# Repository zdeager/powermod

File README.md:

# PowerMOD

A generic power scheduler, UPS, and battery supply for I2C-capable hosts — Linux SBCs, microcontrollers, anything with a 3.3V I2C bus and a power input to control. Real-time clock, scheduled power-cycling, battery backup with load switchover, opt-in watchdog, and an event log, at a component cost of ≈$2.90.

**Status: design complete on paper. No hardware exists yet.** Every part is selected, priced, and datasheet-verified; every net is mapped pin-for-pin; the register map is ready for firmware review. Next step: transcribe the netlist into an EDA tool and lay out the board.

## Documents

| File | What it is |
|---|---|
| [powermod-spec.md](powermod-spec.md) | **The source of truth.** Full decision record with reasoning history — including reversed decisions, retained and marked. Carries the net map, the semantic-review findings, and a 45-claim verification register (every part capability cited to its datasheet; 18 claims were false and each correction is documented) |
| [powermod-user-guide-draft.md](powermod-user-guide-draft.md) | Draft user manual — integration guide, LED states, scheduling patterns, FAQ, and honest limits (drift table, output-current table, weak-supply behavior) |
| [powermod-register-map.md](powermod-register-map.md) | I2C protocol v1 — 32 registers, wire-level reference for host integration and firmware |
| [powermod-schematic.md](powermod-schematic.md) | Pin-exact netlist — every component pin to every net, MCU pin assignment, capture-time checklist. The EDA schematic transcribes this |
| [powermod-bom.md](powermod-bom.md) | Bill of materials — LCSC part numbers, verified prices, do-not-substitute notes, sourcing flags |
| [powermod_full_state_machine.svg](powermod_full_state_machine.svg) | Power state machine — all states, transitions, and gating rules |
| [hardware/](hardware/) | KiCad transcription — `netlist.py` (machine source of truth + validator) generates `powermod.net`, `powermod.kicad_sch` (ERC-clean, round-trip-verified), and via `layout.py` a placed, DRC-clean `powermod.kicad_pcb` (routing pending) |

## Open items (all require hardware)

Converter efficiency, standby current, the `CE` battery-detect decay test, factory-reset gesture feel, Q1/Q2 handover scope check.

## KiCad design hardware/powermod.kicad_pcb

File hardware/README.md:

# PowerMOD hardware

Machine-generated PCB design for a Raspberry Pi Zero 2 W power scheduler /
UPS / battery board. The electrical design is defined in code (`netlist.py`);
the board was laid out and routed with the scripted KiCad + Freerouting
toolchain below, then hand-finished.

## The board — `powermod.kicad_pcb` (final)

65 × 40 mm, 4-layer (F.Cu signal / In1 solid GND / In2 signal / B.Cu signal).
Bolts under a Pi Zero 2 W (holes on the Pi's 58×23 grid, flush to the N+W
edges); the Pi covers y0–30, and all user-facing parts (USB-C out, battery,
button, LEDs, jumpers, test pads) sit on the exposed strip below it.
Single-sided assembly.

One KiCad project, one stem: `powermod.kicad_pro` (netclasses + DRC config),
`powermod.kicad_sch` (generated schematic), `powermod.kicad_pcb` (board),
`powermod.kicad_dru` (width-enforcement rules — net classes alone are NOT
checked by DRC).

**Status: fab-ready.** Fully routed, 0 unconnected, 0 clearance; the only DRC
items are 4 `track_width` flags on the L2/L1N necks at U3's 0.65 mm pins,
which physically cannot be 1.0 mm wide. Pre-fab audit (pad-for-pad netlist
diff, datasheet pin checks, operating-point math, the D5 supercap fix):
see **`PREFAB_AUDIT.md`** — read it before ordering (BOM traps, firmware
contract, bring-up plan).

> **Do NOT regenerate this board from `netlist.py`.** Placement and the
> USB-C fine-pitch escapes are hand-done. Make changes surgically on
> `powermod.kicad_pcb` and update `netlist.py` in parallel, then prove they
> agree with a pad-diff (the audit doc describes it).

## Electrical source of truth

- **`netlist.py`** — every component, pin, and net (73 components, 45 nets).
  Run it to (re)generate `powermod.kicad_sch`, `powermod.net`,
  `powermod.kicad_sym`, `sym-lib-table`, `fp-lib-table`. Has a self-test
  (golden vectors, pin counts).
- **`powermod.pretty/`** — local footprint lib: the merged-pad USB-C
  receptacle (reversible twin pads share one pad, so VBUS/GND escape cleanly
  and DRC sees no coincident-pad conflicts). Required to open the board.

## Reusable tools

All the layout/routing/placement scripts live in **`tools/`** (run them from
this directory, e.g. `python3 tools/finish_board.py powermod.kicad_pcb`, so
board paths and `_sizes.json` resolve; they add the parent dir to `sys.path`
to import `netlist.py`). `netlist.py` itself stays here — it's the design
source and writes the deliverables alongside itself. SPICE decks are in
`tools/spice/`.

Routing pipeline (for derivative boards — not this one):
- **`fr_pipeline.py`** — strip copper + export Specctra DSN / import routed
  SES. Freerouting must never see a pre-routed board.
- `tools/freerouting.jar` (gitignored, ~55 MB) — the autorouter. Java 21+, run
  with `-Djava.awt.headless=true` or it hangs on macOS.
- **`finish_board.py`** — post-route finisher: SES import → GND stitching →
  floating-pour-island tie vias → zone refill. Then DRC with
  `--refill-zones` (without it you get hundreds of phantom violations).
- **`stitch_gnd.py`** — the 2.5 mm GND stitching-via grid to the In1 plane.
- **`close_nets.py`** — route leftover nets with the In2-capable grid A*,
  each route validated by refill+DRC and reverted if it doesn't improve.
- **`router.py`** — grid A* + obstacle model (F/In2/B) used by the above.
- **`netclasses.py`** — inject net-class width targets into a `.kicad_pro`.

Placement:
- **`layout_v2.py`** — the board generator (`gen_pcb`: footprints, GND
  planes, keepouts). `layout_mount.py` configures it for this board's
  outline/holes/pinned I/O.
- **`place_constrained.py`** — constraint-aware force-directed placer
  (net springs, padded repulsion, wide-net/IC halos, rigid converter block).
- **`place_search_mount.py`** / **`relax_mount.py`** — placement search
  scored by Freerouting / overlap relaxer. **`mount_best.py`** — placer
  output snapshot (stale vs the hand-edited board; the board is
  authoritative).
- **`place_check.py`** — courtyard-overlap + off-board report.
- **`make_stencil.py`** — generates a bare user-facing-parts canvas for
  human I/O placement (its output board was removed once the layout froze).
- `_sizes.json` — cached footprint courtyard sizes (kept in this dir; the
  placer reads it cwd-relative).

SPICE (`tools/spice/`):
- **`power_path_scenarios.py`** — behavioural ngspice model of the Q1/Q2/Q3
  power path; runs the startup/switchover/unplug scenario matrix (see the
  SPICE section of `PREFAB_AUDIT.md`). Needs `ngspice` on PATH.

## Hard-won rules (cost real time — don't relearn them)

- A green DRC only checks rules that exist: keep `powermod.kicad_dru` next
  to the board, and after any rename/move confirm the 4 known `track_width`
  flags still fire (if they vanish, the rules got orphaned, not fixed).
- Netclasses live in the `.kicad_pro`. A board file copied away from its
  project routes everything at 0.2 mm and "routes fully" — a fake win.
- Zone fills are stored in the file: refill before DRC or judging renders.
- Scripted tracks don't bind to large connector pads (USB-C, bar pads) —
  those few escapes are interactive-routing territory; small pads bind fine.

## History

v1 (58×40, 2-layer) had 3A rails at 0.2 mm (the `.kicad_dru` lesson); v2
(65×30) was superseded by this board; the QFN-package MCU was swapped for the
SOIC-20 ATtiny1616 to break the routing wall; `powermod_mount.*` was renamed
to `powermod.*` once it became the only board (2026-07-17); then the MCU
migrated **ATtiny1616 → PY32F003F18P6** (TSSOP-20, ARM Cortex-M0+) on the
`instock-parts` branch (2026-07-18) for JLC assembly availability, with a full
reroute — the current board is 65×40, 4-layer, PY32. Lessons live in
the tools and `PREFAB_AUDIT.md`, not in stale board files.

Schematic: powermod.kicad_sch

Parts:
C1, C2, C7: 10u; C_0805_2012Metric
C3, C4, C5: 22u; C_0805_2012Metric
C6: 4.7u; C_0603_1608Metric
C8, C9: 1u; C_0603_1608Metric
C10, C11, C12, C13, C14, C15, C16: 100n; C_0402_1005Metric
D1, D2: TJ-S3227; LED_TJ-S3227_RG_3.2x2.7mm
D3, D4, D5: 1N4148WS; D_SOD-323
J1: USB_C_IN; USB_C_Receptacle_TYPE-C_16P_PowerMerged
J2: USB_C_OUT; USB_C_Receptacle_TYPE-C_16P_PowerMerged
J3: JST_PH_2; JST_PH_S2B-PH-K_1x02_P2.00mm_Horizontal
J4: STEMMA_QT; JST_SH_SM04B-SRSS-TB_1x04-1MP_P1.00mm_Horizontal
J5: SWD_HDR; PinHeader_1x04_P2.54mm_Vertical
JP1: CHG_JUMPER; SolderJumper-2_P1.3mm_Open_RoundedPad1.0x1.5mm
JP2: VSEL_JUMPER; SolderJumper-2_P1.3mm_Open_RoundedPad1.0x1.5mm
L1: 1.5uH; L_Sumida_CDMC6D28_7.25x6.5mm
Q1, Q2: AON7407; DFN-8-1EP_3x3mm_P0.65mm_EP1.6x2.56mm
Q3: BSS138; SOT-23
R1: 1.2k; R_0402_1005Metric
R2, R3: 5.1k; R_0402_1005Metric
R4, R5: 56k; R_0402_1005Metric
R6, R8, R25: 1M; R_0402_1005Metric
R7, R9: 330k; R_0402_1005Metric
R10, R12, R13, R14, R28: 100k; R_0402_1005Metric
R11: 47k; R_0402_1005Metric
R15, R16, R17, R18, R19: 10k; R_0402_1005Metric
R20, R21, R22, R23: 560; R_0402_1005Metric
R24: 180k; R_0402_1005Metric
R26: 620k; R_0402_1005Metric
R27: 1k; R_0402_1005Metric
SW1: BUTTON; SW_SPST_PTS647_Sx50
TP1: VBACKUP_PAD; TestPoint_Pad_2.0x2.0mm
TP2: BAT_PAD; TestPoint_Pad_2.0x2.0mm
TP3: VOUT_PAD; TestPoint_Pad_2.0x2.0mm
TP4: GND_PAD; TestPoint_Pad_2.0x2.0mm
TP5: VBACKUP_GND_PAD; TestPoint_Pad_2.0x2.0mm
TP6: VOUT_GND_PAD; TestPoint_Pad_2.0x2.0mm
U1: BM8563ESA; SOIC-8_3.9x4.9mm_P1.27mm
U2: PY32F003F18P6; TSSOP-20_4.4x6.5mm_P0.65mm
U3: TPS63020DSJR; VSON-14-1EP_3x4.45mm_P0.65mm_EP1.6x4.2mm
U4: TP4056; SOIC-8-1EP_3.9x4.9mm_P1.27mm_EP2.29x3mm
U5: XC6206P332MR; SOT-23
Y1: Q13FC13500004; Crystal_SMD_3215-2Pin_3.2x1.5mm

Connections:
3V3: C9.1, C14.1, D3.2 (A), R15.1, R16.1, R17.1, R18.1, R19.1, R27.1, U2.9 (VDD), U5.2 (VOUT)
BUTTON: SW1.1 (A), U2.20 (PA1/BUTTON)
CC1_IN: J1.A5 (CC1), R2.1
CC1_OUT: J2.A5 (CC1), R5.1
CC2_IN: J1.B5 (CC2), R3.1
CC2_OUT: J2.B5 (CC2), R4.1
CHG_CE: R28.2, U2.5 (PA6/CHG_CE), U4.8 (CE)
CHG_CHRG: R15.2, U2.12 (PB5/CHG_CHRG), U4.7 (CHRG)
CHG_JP: D5.2 (A), R27.2
CHG_JPD: D5.1 (K), JP1.1 (A)
CHG_STDBY: R16.2, U2.6 (PA7/CHG_STDBY), U4.6 (STDBY)
CONV_EN: R14.1, U2.2 (PA3/CONV_EN), U3.12 (EN)
D1_GRN: D1.2 (A_GRN), R21.2
D1_RED: D1.3 (A_RED), R20.2
D2_GRN: D2.2 (A_GRN), R23.2
D2_RED: D2.3 (A_RED), R22.2
FB: R24.1, R25.1, U3.3 (FB)
FB_MID: JP2.1 (A), R25.2, R26.1
GND: C1.2, C2.2, C3.2, C4.2, C5.2, C6.2, C7.2, C8.2, C9.2, C10.2, C11.2, C13.2, C14.2, C15.2, C16.2, D1.1 (K_GRN), D1.4 (K_RED), D2.1 (K_GRN), D2.4 (K_RED), J1.A1 (GND), J1.A12 (GND), J1.SH (SHIELD), J2.A1 (GND), J2.A12 (GND), J2.SH (SHIELD), J3.2 (BAT-), J4.1 (GND), J5.1 (GND), Q3.2 (S), R1.2, R2.2, R3.2, R7.2, R9.2, R12.2, R13.2, R14.2, R24.2, SW1.2 (B), TP4.1, TP5.1, TP6.1, U1.4 (VSS), U2.7 (VSS), U3.2 (GND), U3.13 (PS/SYNC), U3.15 (PGND), U4.1 (TEMP), U4.3 (GND), U4.9 (PAD), U5.1 (VSS)
L1N: L1.1, U3.8 (L1), U3.9 (L1)
L2: L1.2, U3.6 (L2), U3.7 (L2)
LED_BAT_A: J5.3 (SWDIO), R22.1, U2.10 (PA13/SWDIO/LED_BAT_A)
LED_BAT_B: J5.2 (SWCLK), R23.1, U2.11 (PA14/SWCLK/LED_BAT_B)
LED_PWR_A: R20.1, U2.19 (PA0/LED_PWR_A)
LED_PWR_B: R21.1, U2.15 (PF4/BOOT0/LED_PWR_B)
NRST: J5.4 (NRST), U2.18 (PF2/NRST)
OSCI: U1.1 (OSCI), Y1.1 (X1)
OSCO: U1.2 (OSCO), Y1.2 (X2)
PROG: R1.1, U4.2 (PROG)
Q1_GATE: C12.2, Q1.4 (G), R10.2, R11.1
Q1_GATE_DRV: Q3.1 (G), R13.1, U2.1 (PA2/Q1_GATE_DRV)
Q3_DRAIN: Q3.3 (D), R11.2
RTC_INT: R19.2, U1.3 (INT), U2.8 (PA12/RTC_INT)
RTC_SCL: R18.2, U1.6 (SCL), U2.17 (PF1/RTC_SCL)
RTC_SDA: R17.2, U1.5 (SDA), U2.16 (PF0/RTC_SDA)
RTC_VDD: C13.1, D3.1 (K), D4.1 (K), U1.8 (VDD)
SCL: J4.4 (SCL), U2.13 (PB6/I2C_SCL)
SDA: J4.3 (SDA), U2.14 (PB7/I2C_SDA)
VBACKUP: D4.2 (A), JP1.2 (B), TP1.1
VBAT: C6.1, J3.1 (BAT+), Q2.5 (D), Q2.6 (D), Q2.7 (D), Q2.8 (D), Q2.9 (D), R6.1, TP2.1, U4.5 (BAT)
VBAT_DIV: C10.1, R6.2, R7.1, U2.3 (PA4/VBAT_SENSE)
VBUS: C7.1, C15.1, J1.A4 (VBUS), J1.A9 (VBUS), Q1.5 (D), Q1.6 (D), Q1.7 (D), Q1.8 (D), Q1.9 (D), Q2.4 (G), R8.1, R12.1, R28.1, U4.4 (VCC)
VBUS_DIV: C11.1, R8.2, R9.1, U2.4 (PA5/VBUS_SENSE)
VOUT: C3.1, C4.1, C5.1, J2.A4 (VBUS), J2.A9 (VBUS), JP2.2 (B), R4.2, R5.2, R26.2, TP3.1, U3.4 (VOUT), U3.5 (VOUT)
VSYS: C1.1, C2.1, C8.1, C12.1, C16.1, Q1.1 (S), Q1.2 (S), Q1.3 (S), Q2.1 (S), Q2.2 (S), Q2.3 (S), R10.1, U3.1 (VINA), U3.10 (VIN), U3.11 (VIN), U5.3 (VIN)

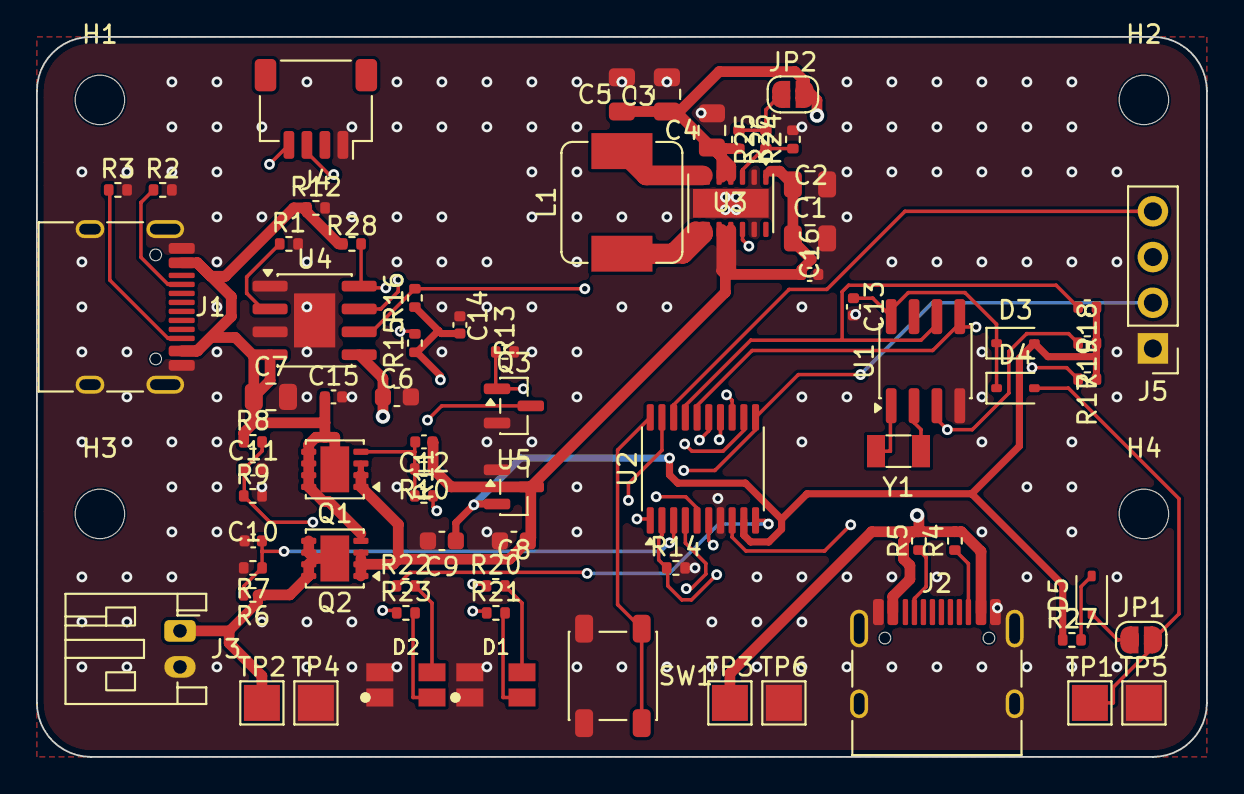
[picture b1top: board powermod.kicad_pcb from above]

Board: 4 copper layers, 65.0 x 40.0 mm, 77 parts (0 on the bottom side), 45 nets.

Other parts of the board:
H1, H2, H3, H4: M2.5; MountingHole_2.7mm_M2.5

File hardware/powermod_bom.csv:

"Comment","Designator","Footprint","LCSC Part #"
"10u","C1,C2,C7","C_0805_2012Metric","C15850"
"100n","C10,C11,C12,C13,C14,C15,C16","C_0402_1005Metric","C1525"
"22u","C3,C4,C5","C_0805_2012Metric","C45783"
"4.7u","C6","C_0603_1608Metric","C19666"
"1u","C8,C9","C_0603_1608Metric","C5673"
"TJ-S3227","D1,D2","LED_TJ-S3227_RG_3.2x2.7mm","C601677"
"1N4148WS","D3,D4,D5","D_SOD-323","C51898295"
"USB_C_IN","J1","USB_C_Receptacle_TYPE-C_16P_PowerMerged","C165948"
"USB_C_OUT","J2","USB_C_Receptacle_TYPE-C_16P_PowerMerged","C165948"
"JST_PH_2","J3","JST_PH_S2B-PH-K_1x02_P2.00mm_Horizontal",""
"STEMMA_QT","J4","JST_SH_SM04B-SRSS-TB_1x04-1MP_P1.00mm_Horizontal","C51940130"
"SWD_HDR","J5","PinHeader_1x04_P2.54mm_Vertical",""
"1.5uH","L1","L_Sumida_CDMC6D28_7.25x6.5mm","C5189751"
"AON7407","Q1,Q2","DFN-8-1EP_3x3mm_P0.65mm_EP1.6x2.56mm","C176756"
"BSS138","Q3","SOT-23","C52895"
"1.2k","R1","R_0402_1005Metric","C25862"
"100k","R10,R12,R13,R14,R28","R_0402_1005Metric","C25741"
"47k","R11","R_0402_1005Metric","C25792"
"10k","R15,R16,R17,R18,R19","R_0402_1005Metric","C25744"
"5.1k","R2,R3","R_0402_1005Metric","C25905"
"560","R20,R21,R22,R23","R_0402_1005Metric","C25126"
"180k","R24","R_0402_1005Metric","C25760"
"620k","R26","R_0402_1005Metric","C270590"
"1k","R27","R_0402_1005Metric","C11702"
"56k","R4,R5","R_0402_1005Metric","C25796"
"1M","R6,R8,R25","R_0402_1005Metric","C26083"
"330k","R7,R9","R_0402_1005Metric","C25778"
"BUTTON","SW1","SW_SPST_PTS647_Sx50","C2799414"
"BM8563ESA","U1","SOIC-8_3.9x4.9mm_P1.27mm","C269877"
"PY32F003F18P6","U2","TSSOP-20_4.4x6.5mm_P0.65mm","C5379864"
"TPS63020DSJR","U3","VSON-14-1EP_3x4.45mm_P0.65mm_EP1.6x4.2mm","C15483"
"TP4056","U4","SOIC-8-1EP_3.9x4.9mm_P1.27mm_EP2.29x3mm","C382139"
"XC6206P332MR","U5","SOT-23","C5446"
"Q13FC13500004","Y1","Crystal_SMD_3215-2Pin_3.2x1.5mm","C32346"

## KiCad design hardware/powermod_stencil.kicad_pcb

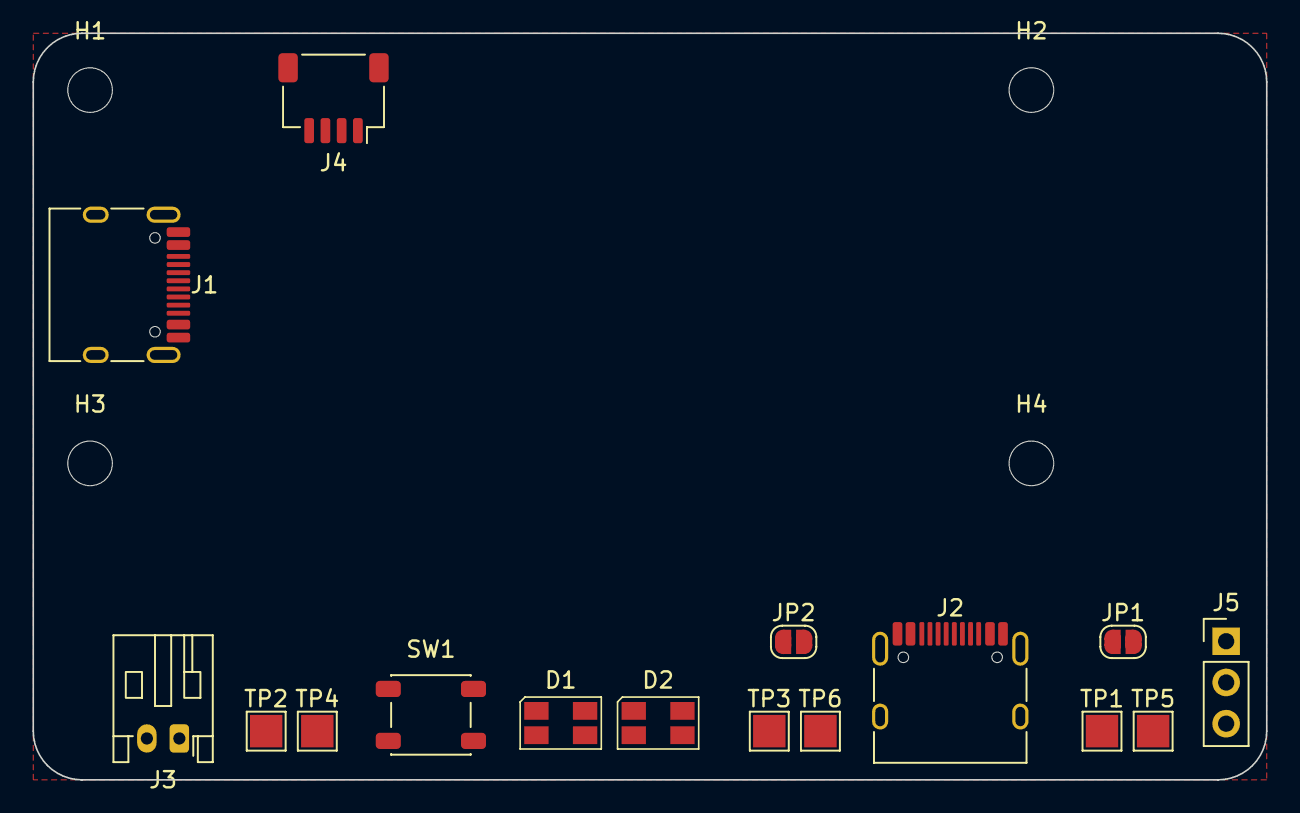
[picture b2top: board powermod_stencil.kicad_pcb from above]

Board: 4 copper layers, 76.0 x 46.0 mm, 20 parts (0 on the bottom side), 5 nets, no tracks yet.

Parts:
D1, D2: LED_RG_PLCC4; LED_Avago_PLCC4_3.2x2.8mm_CW
H1, H2, H3, H4: M2.5; MountingHole_2.7mm_M2.5
J1: USB_C_IN; USB_C_Receptacle_HRO_TYPE-C-31-M-12
J2: USB_C_OUT; USB_C_Receptacle_HRO_TYPE-C-31-M-12
J3: JST_PH_2; JST_PH_S2B-PH-K_1x02_P2.00mm_Horizontal
J4: STEMMA_QT; JST_SH_SM04B-SRSS-TB_1x04-1MP_P1.00mm_Horizontal
J5: UPDI_HDR; PinHeader_1x03_P2.54mm_Vertical
JP1: CHG_JUMPER; SolderJumper-2_P1.3mm_Open_RoundedPad1.0x1.5mm
JP2: VSEL_JUMPER; SolderJumper-2_P1.3mm_Open_RoundedPad1.0x1.5mm
SW1: BUTTON; SW_SPST_PTS647_Sx50
TP1: VBACKUP_PAD; TestPoint_Pad_2.0x2.0mm
TP2: BAT_PAD; TestPoint_Pad_2.0x2.0mm
TP3: VOUT_PAD; TestPoint_Pad_2.0x2.0mm
TP4: GND_PAD; TestPoint_Pad_2.0x2.0mm
TP5: VBACKUP_GND_PAD; TestPoint_Pad_2.0x2.0mm
TP6: VOUT_GND_PAD; TestPoint_Pad_2.0x2.0mm

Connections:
GND: D1.2, D1.4, D2.2, D2.4, J1.A1, J1.A12, J1.B1, J1.B12, J2.A1, J2.A12, J2.B1, J2.B12, J3.2, J4.1, J5.3, SW1.2, TP4.1, TP5.1, TP6.1
VBACKUP: JP1.2, TP1.1
VBAT: J3.1, TP2.1
VBUS: J1.A4, J1.A9, J1.B4, J1.B9
VOUT: J2.A4, J2.A9, J2.B4, J2.B9, JP2.2, TP3.1

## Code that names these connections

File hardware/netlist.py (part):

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 # in any package — the whole tinyAVR 1-series AND megaAVR-0 line are <~100 units
 # each, all Extended (checked 2026-07-18). Pinout transcribed from the LCSC/
 # EasyEDA symbol (C5379864) verified 2026-07-18. Constraints honoured:
 #   ADC  -> PA4/PA5 (ADC_IN4/5)          HW I2C1 -> PB6/PB7 (STEMMA bus)
 #   RTC I2C bit-banged -> PF0/PF1        SWD -> PA13/PA14, shared with the 2 BAT
 #   LEDs (LEDs tolerate SWD idle; debugger connects under reset via NRST=PF2 on
 #   the header). BOOT0=PF4 carries an LED OUTPUT only (Hi-Z at reset -> internal
 #   pull-down -> boots flash; never put an input on BOOT0). 0 spare pins.
 # ADC ref = VDD (3.3V, the XC6206 rail). Existing 1M/330k dividers peak at
 # VBUS 5.25V->1.30V, VBAT 4.25V->1.05V: no clip, ~1.6k/1.3k of 4096 counts
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 # internal bandgap if needed. Net names are IDENTICAL to the ATtiny mapping
 # (only pin assignment moved) except UPDI dropped / NRST added.
 'U2': ('PY32F003F18P6', 'Package_SO:TSSOP-20_4.4x6.5mm_P0.65mm', 'C5379864', {
   '1':('PA2/Q1_GATE_DRV','Q1_GATE_DRV'), '2':('PA3/CONV_EN','CONV_EN'),
   '3':('PA4/VBAT_SENSE','VBAT_DIV'),     '4':('PA5/VBUS_SENSE','VBUS_DIV'),
   '5':('PA6/CHG_CE','CHG_CE'),           '6':('PA7/CHG_STDBY','CHG_STDBY'),
   '7':('VSS','GND'),                     '8':('PA12/RTC_INT','RTC_INT'),
   '9':('VDD','3V3'),                     '10':('PA13/SWDIO/LED_BAT_A','LED_BAT_A'),
   '11':('PA14/SWCLK/LED_BAT_B','LED_BAT_B'), '12':('PB5/CHG_CHRG','CHG_CHRG'),
   '13':('PB6/I2C_SCL','SCL'),            '14':('PB7/I2C_SDA','SDA'),
   '15':('PF4/BOOT0/LED_PWR_B','LED_PWR_B'), '16':('PF0/RTC_SDA','RTC_SDA'),
   '17':('PF1/RTC_SCL','RTC_SCL'),        '18':('PF2/NRST','NRST'),
   '19':('PA0/LED_PWR_A','LED_PWR_A'),    '20':('PA1/BUTTON','BUTTON')}),
 'U3': ('TPS63020DSJR', 'Package_SON:VSON-14-1EP_3x4.45mm_P0.65mm_EP1.6x4.2mm', 'C15483', {
   '1':('VINA','VSYS'), '2':('GND','GND'), '3':('FB','FB'), '4':('VOUT','VOUT'),
   '5':('VOUT','VOUT'), '6':('L2','L2'), '7':('L2','L2'), '8':('L1','L1N'),
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   '8':('CE','CHG_CE'), '9':('PAD','GND')}),
 # Pinout VERIFIED 2026-07-19 vs Torex XC6206 datasheet: the XC6206 has TWO
 # pin variants (MR vs PR). Ours is the -MR- package (C5446 = XC6206P332MR-G),
 # whose SOT-23 assignment is pin1=VSS, pin2=VOUT, pin3=VIN -> matches below.
 # (The PR package differs; do NOT copy this to a PR part.)
 'U5': ('XC6206P332MR', FP['SOT'], 'C5446', {
   '1':('VSS','GND'), '2':('VOUT','3V3'), '3':('VIN','VSYS')}),
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 'R22':R('560','LED_BAT_A','D2_RED'), 'R23':R('560','LED_BAT_B','D2_GRN'),
 'R24':R('180k','FB','GND'), 'R25':R('1M','FB','FB_MID'), 'R26':R('620k','FB_MID','VOUT'),
 'R27':R('1k','3V3','CHG_JP'),          # supercap charge, behind JP1
 'R28':R('100k','VBUS','CHG_CE'),       # CE default-ON: TP4056 charges even with the MCU in reset/unprogrammed (2026-07-16); MCU PC4 push-pull overrides
 'C1': C('10u','VSYS','GND','C08'),  'C2': C('10u','VSYS','GND','C08'),
 'C3': C('22u','VOUT','GND','C08'),  'C4': C('22u','VOUT','GND','C08'),
 'C5': C('22u','VOUT','GND','C08'),
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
